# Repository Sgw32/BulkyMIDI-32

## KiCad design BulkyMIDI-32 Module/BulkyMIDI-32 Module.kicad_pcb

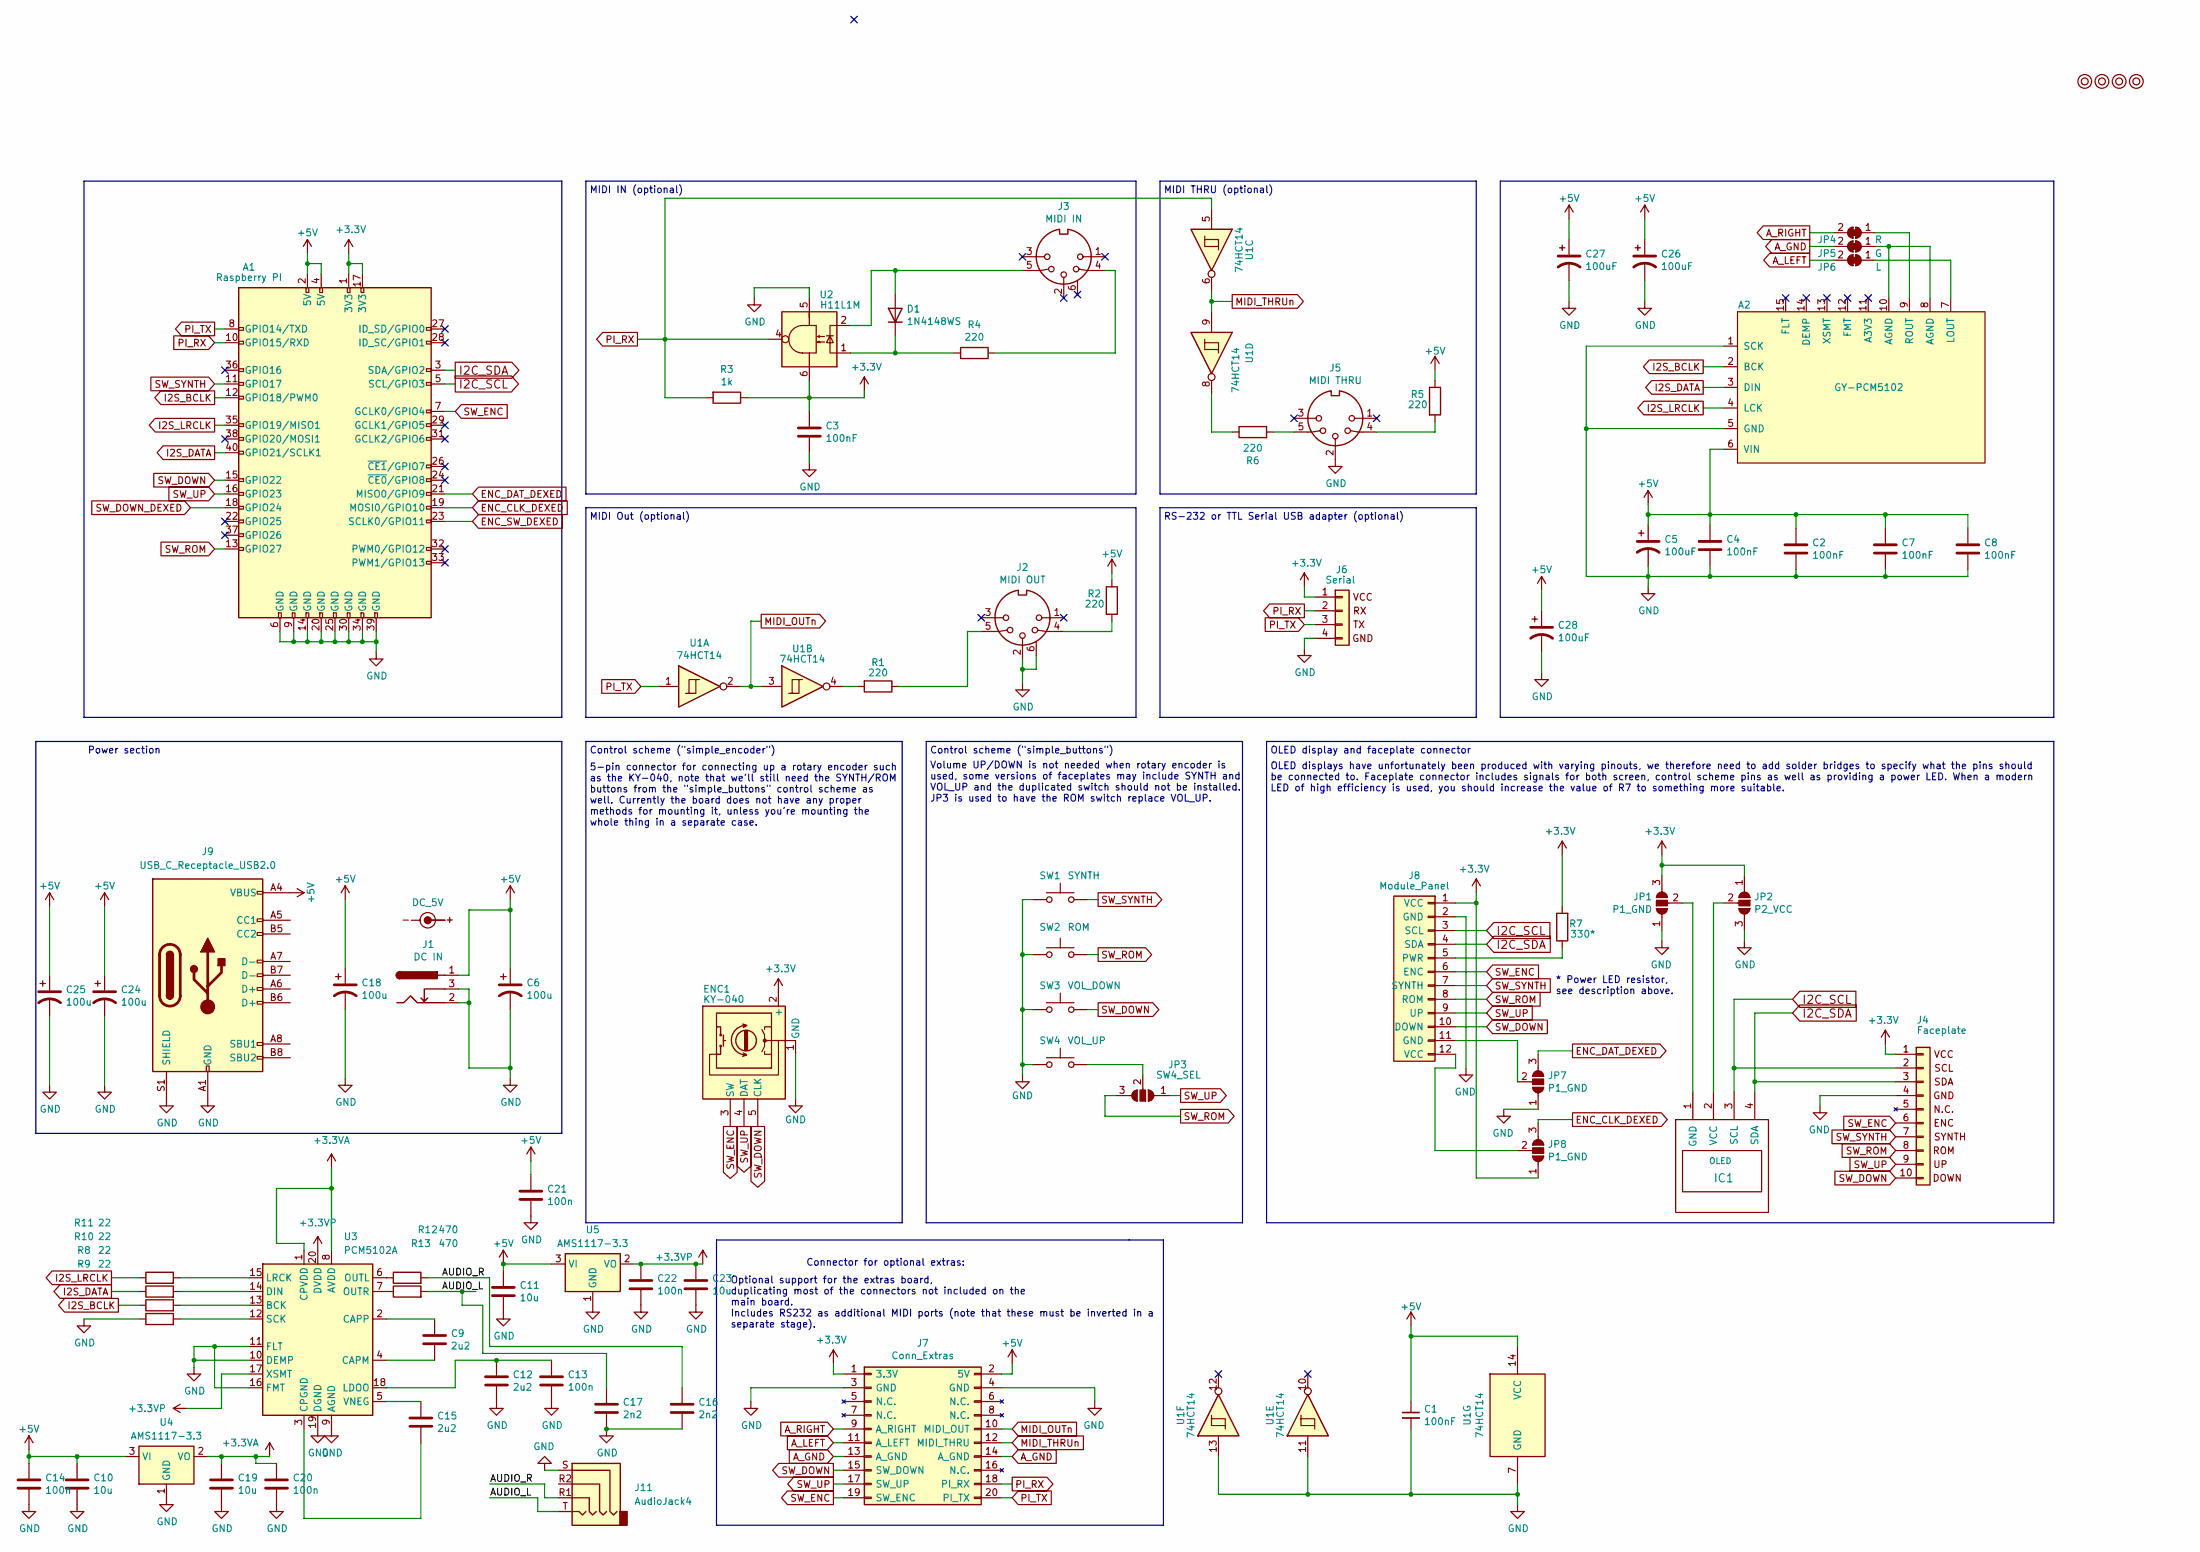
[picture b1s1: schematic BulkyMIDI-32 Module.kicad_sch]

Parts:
A1: Raspberry PI; Raspberry_Pi_3B_Socketed_THT_FaceDown_MountingHoles
A2: GY-PCM5102
C1, C2, C3, C4, C7, C8: 100nF; C_0402_1005Metric
C5, C26, C27, C28: 100uF; CP_EIA-3528-21_Kemet-B
C6, C18, C24, C25: 100u; CP_EIA-3528-21_Kemet-B
C9, C12, C15: 2u2; C_0402_1005Metric
C10, C11, C19, C23: 10u; C_0402_1005Metric
C13, C14, C20, C21, C22: 100n; C_0402_1005Metric
C16, C17: 2n2; C_0402_1005Metric
D1: 1N4148WS; D_SOD-323
ENC1: KY-040; PinHeader_1x05_P2.54mm_Horizontal
IC1: OLED; 1.3_I2C_OLED_No_mounting
J1: DC IN; BarrelJack_CLIFF_FC681465S_SMT_Horizontal
J2: MIDI OUT; DIN5_MIDI_OUT
J3: MIDI IN; DIN5_MIDI_IN
J4: Faceplate; PinSocket_1x10_P2.54mm_Vertical
J5: MIDI THRU; PinHeader_1x05_P2.54mm_Horizontal
J6: Serial; PinHeader_1x04_P2.54mm_Horizontal
J7: Conn_Extras; PinSocket_2x10_P2.54mm_Vertical
J8: Module_Panel
J9: USB_C_Receptacle_USB2.0; USB_C_Receptacle_XKB_U262-16XN-4BVC11
J11: AudioJack4; Jack_3.5mm_PJ320D_Horizontal
JP1, JP7, JP8: P1_GND; SolderJumper-3_P1.3mm_Open_RoundedPad1.0x1.5mm
JP2: P2_VCC; SolderJumper-3_P1.3mm_Open_RoundedPad1.0x1.5mm
JP3: SW4_SEL; SolderJumper-3_P1.3mm_Open_RoundedPad1.0x1.5mm
JP4: R; SolderJumper-2_P1.3mm_Open_TrianglePad1.0x1.5mm
JP5: G; SolderJumper-2_P1.3mm_Open_TrianglePad1.0x1.5mm
JP6: L; SolderJumper-2_P1.3mm_Open_TrianglePad1.0x1.5mm
M1, M2, M3, M4: Mounting; M3
R1, R2, R4, R5, R6: 220; R_0805_2012Metric
R3: 1k; R_0805_2012Metric
R7: 330*; R_0805_2012Metric
R8, R9, R10, R11: 22; R_0402_1005Metric
R12, R13: 470; R_0402_1005Metric
SW1: SYNTH; SW_Tactile_SPST_Angled_PTS645Vx39-2LFS
SW2: ROM; SW_Tactile_SPST_Angled_PTS645Vx39-2LFS
SW3: VOL_DOWN; SW_Tactile_SPST_Angled_PTS645Vx39-2LFS
SW4: VOL_UP; SW_Tactile_SPST_Angled_PTS645Vx39-2LFS
SYM1: DC_5V; PWR_Specification
U1: 74HCT14; SO-14_3.9x8.65mm_P1.27mm
U2: H11L1M; DIP-6_W7.62mm
U3: PCM5102A; TSSOP-20_4.4x6.5mm_P0.65mm
U4, U5: AMS1117-3.3; SOT-223-3_TabPin2

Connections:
+3.3VA: C19.1, C20.1, U3.1 (CPVDD), U3.8 (AVDD), U4.2 (VO)
+3.3VP: C22.1, C23.1, U3.17 (XSMT), U3.20 (DVDD), U5.2 (VO)
+3V3: A1.1 (3V3), A1.17 (3V3), C3.1, ENC1.2 (+), J4.1 (VCC), J6.1, J7.1 (3.3V), J8.1 (VCC), JP1.3 (B), JP2.1 (A), JP8.1 (A), R3.1, R7.2, U2.6
+5V: A1.2 (5V), A1.4 (5V), A2.6 (VIN), C1.1, C2.1, C4.1, C5.1, C6.1, C7.1, C8.1, C10.1, C11.1, C14.1, C18.1, C21.1, C24.1, C25.1, C26.1, C27.1, C28.1, J1.1, J7.2 (5V), J9.A4 (VBUS), J9.A9 (VBUS), J9.B4 (VBUS), J9.B9 (VBUS), R2.1, R5.1, U1.14 (VCC), U4.3 (VI), U5.3 (VI)
/AUDIO_L: C17.1, J11.T, R13.2
/AUDIO_R: C16.1, J11.R1, R12.2
A_GND: J7.13 (A_GND), J7.14 (A_GND), JP5.2 (B)
A_LEFT: J7.11 (A_LEFT), JP6.2 (B)
A_RIGHT: J7.9 (A_RIGHT), JP4.2 (B)
ENC_CLK_DEXED: A1.19 (MOSI0/GPIO10), JP8.3 (B)
ENC_DAT_DEXED: A1.21 (MISO0/GPIO9), JP7.3 (B)
ENC_SW_DEXED: A1.23 (SCLK0/GPIO11)
GND: A1.6 (GND), A1.9 (GND), A1.14 (GND), A1.20 (GND), A1.25 (GND), A1.30 (GND), A1.34 (GND), A1.39 (GND), A2.1 (SCK), A2.5 (GND), C1.2, C2.2, C3.2, C4.2, C5.2, C6.2, C7.2, C8.2, C10.2, C11.2, C12.2, C13.2, C14.2, C16.2, C17.2, C18.2, C19.2, C20.2, C21.2, C22.2, C23.2, C24.2, C25.2, C26.2, C27.2, C28.2, ENC1.1 (GND), J1.2, J1.3, J2.2, J2.6, J4.4, J5.2, J6.4, J7.3 (GND), J7.4 (GND), J8.2 (GND), J9.A1 (GND), J9.A12 (GND), J9.B1 (GND), J9.B12 (GND), J9.S1 (SHIELD), J11.S, JP1.1 (A), JP2.3 (B), JP7.1 (A), R11.1, SW1.1, SW2.1, SW3.1, SW4.1, U1.7 (GND), U1.11, U1.13, U2.5, U3.9 (AGND), U3.10 (DEMP), U3.11 (FLT), U3.16 (FMT), U3.19 (DGND), U4.1 (GND), U5.1 (GND)
I2C_SCL: A1.5 (SCL/GPIO3), IC1.3 (SCL), J4.2, J8.3 (SCL)
I2C_SDA: A1.3 (SDA/GPIO2), IC1.4 (SDA), J4.3, J8.4 (SDA)
I2S_BCLK: A1.12 (GPIO18/PWM0), A2.2 (BCK), R10.1
I2S_DATA: A1.40 (GPIO21/SCLK1), A2.3 (DIN), R9.1
I2S_LRCLK: A1.35 (GPIO19/MISO1), A2.4 (LCK), R8.1
MIDI_OUTn: J7.10 (MIDI_OUT), U1.2, U1.3
MIDI_THRUn: J7.12 (MIDI_THRU), U1.6, U1.9
unnamed: A2.7 (LOUT), JP6.1 (A)
unnamed: A2.9 (ROUT), JP4.1 (A)
unnamed: D1.2 (A), J3.5, U2.2
unnamed: D1.1 (K), R4.2, U2.1
unnamed: IC1.1 (GND), JP1.2 (C)
unnamed: IC1.2 (VCC), JP2.2 (C)
unnamed: J2.4, R2.2
unnamed: J2.5, R1.1
unnamed: J3.4, R4.1
unnamed: J5.4, R5.2
unnamed: J5.5, R6.2
unnamed: J8.5 (PWR), R7.1
unnamed: JP3.2 (C), SW4.2
unnamed: A2.8 (AGND), A2.10 (AGND), JP5.1 (A)
unnamed: J8.11 (GND), JP7.2 (C)
unnamed: J8.12 (VCC), JP8.2 (C)
unnamed: R1.2, U1.4
unnamed: R6.1, U1.8
unnamed: R10.2, U3.13 (BCK)
unnamed: C9.2, U3.4 (CAPM)
unnamed: C9.1, U3.2 (CAPP)
unnamed: C15.2, U3.3 (CPGND)
unnamed: R9.2, U3.14 (DIN)
unnamed: C12.1, C13.1, U3.18 (LDOO)
unnamed: R8.2, U3.15 (LRCK)
unnamed: R12.1, U3.6 (OUTL)
unnamed: R13.1, U3.7 (OUTR)
unnamed: R11.2, U3.12 (SCK)
unnamed: C15.1, U3.5 (VNEG)
PI_RX: A1.10 (GPIO15/RXD), J6.2, J7.18 (PI_RX), R3.2, U1.5, U2.4
PI_TX: A1.8 (GPIO14/TXD), J6.3, J7.20 (PI_TX), U1.1
SW_DOWN: A1.15 (GPIO22), ENC1.5 (CLK), J4.10 (GND), J7.15 (SW_DOWN), J8.10 (DOWN), SW3.2
SW_DOWN_DEXED: A1.18 (GPIO24)
SW_ENC: A1.7 (GCLK0/GPIO4), ENC1.3 (SW), J4.6, J7.19 (SW_ENC), J8.6 (ENC)
SW_ROM: A1.13 (GPIO27), J4.8, J8.8 (ROM), JP3.3 (B), SW2.2
SW_SYNTH: A1.11 (GPIO17), J4.7, J8.7 (SYNTH), SW1.2
SW_UP: A1.16 (GPIO23), ENC1.4 (DAT), J4.9, J7.17 (SW_UP), J8.9 (UP), JP3.1 (A)

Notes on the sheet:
OLED display and faceplate connector
Control scheme ("simple_buttons")
MIDI Out (optional)
Control scheme ("simple_encoder")
MIDI THRU (optional)
Power section
Connector for optional extras:
MIDI IN (optional)
5-pin connector for connecting up a rotary encoder such as the KY-040, note that we'll still need the SYNTH/ROM buttons from the "simple_buttons" control scheme as well. Currently the board does not have any proper methods for mounting it, unless you're mounting the whole thing in a separate case.
Optional support for the extras board, duplicating most of the connectors not included on the main board. Includes RS232 as additional MIDI ports (note that these must be inverted in a separate stage).
Volume UP/DOWN is not needed when rotary encoder is used, some versions of faceplates may include SYNTH and VOL_UP and the duplicated switch should not be installed. JP3 is used to have the ROM switch replace VOL_UP.
RS-232 or TTL Serial USB adapter (optional)
* Power LED resistor, see description above.
OLED displays have unfortunately been produced with varying pinouts, we therefore need to add solder bridges to specify what the pins should be connected to. Faceplate connector includes signals for both screen, control scheme pins as well as providing a power LED. When a modern LED of high efficie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

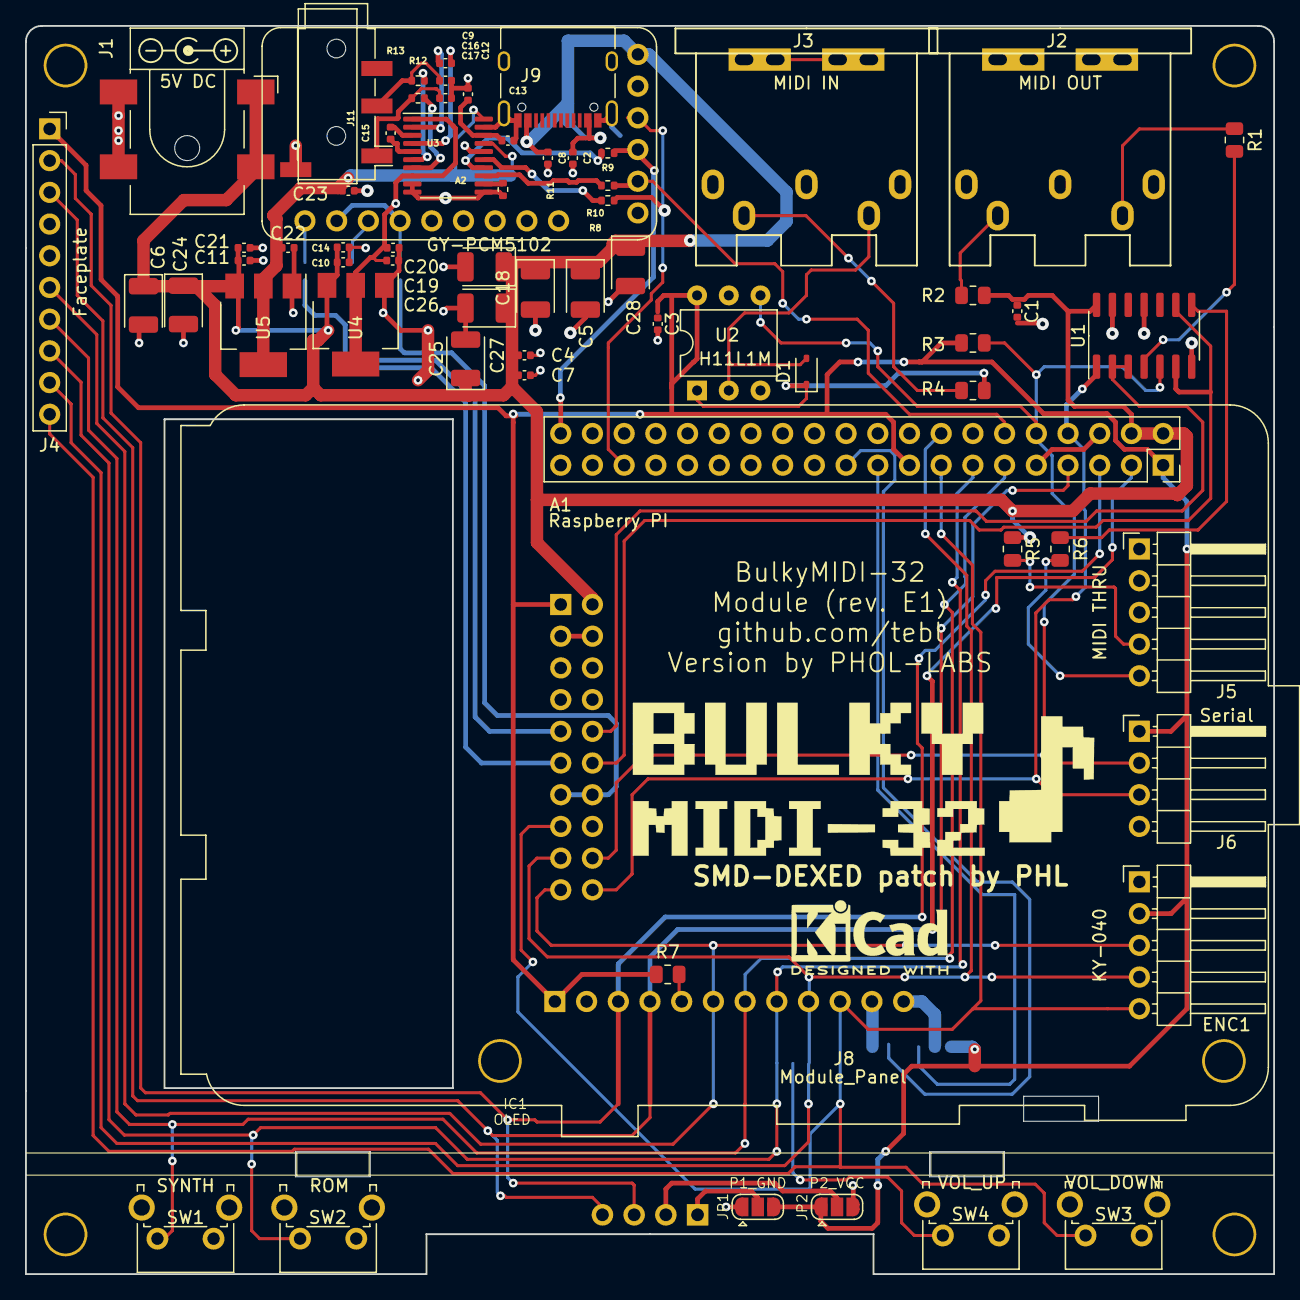
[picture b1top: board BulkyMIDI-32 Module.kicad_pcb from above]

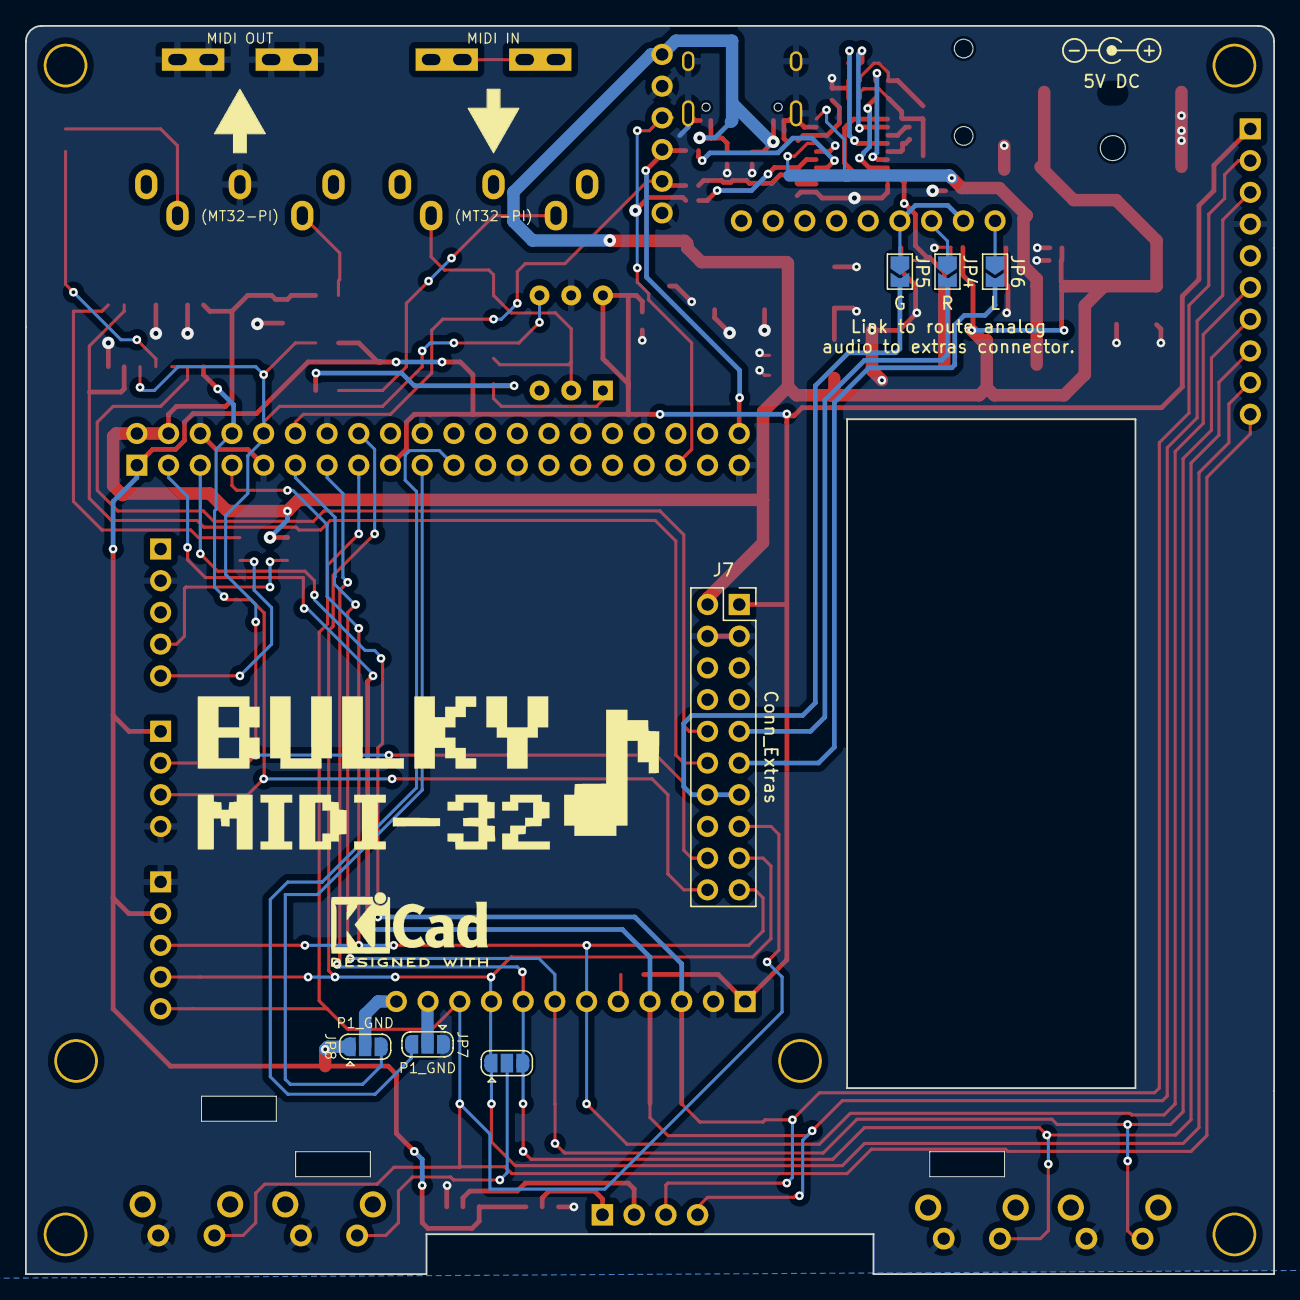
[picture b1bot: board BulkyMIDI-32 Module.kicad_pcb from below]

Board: 2 copper layers, 100.0 x 100.0 mm, 78 parts (7 on the bottom side), 55 nets.

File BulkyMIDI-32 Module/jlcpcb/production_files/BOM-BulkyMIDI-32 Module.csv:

Comment,Designator,Footprint,LCSC
PCM5102A,U3,TSSOP-20_4.4x6.5mm_P0.65mm,C107671
DC IN,J1,BarrelJack_CLIFF_FC681465S_SMT_Horizontal,C114916
2u2,"C12,C15,C9",C_0402_1005Metric,C12530
Raspberry PI,A1,Raspberry_Pi_3B_Socketed_THT_FaceDown_MountingHoles,C132132
100nF,"C1,C13,C14,C2,C20,C21,C22,C3,C4,C7,C8",C_0402_1005Metric,C1525
2n2,"C16,C17",C_0402_1005Metric,C1531
10u,"C10,C11,C19,C23",C_0402_1005Metric,C15525
100u,"C18,C24,C25,C26,C27,C28,C5,C6",CP_EIA-3528-21_Kemet-B,C16133
H11L1M,U2,DIP-6_W7.62mm,C16587
USB_C_Receptacle_USB2.0,J9,USB_C_Receptacle_XKB_U262-16XN-4BVC11,C165948
1k,R3,R_0805_2012Metric,C17513
220,"R1,R2,R4,R5,R6",R_0805_2012Metric,C17557
330*,R7,R_0805_2012Metric,C17630
1N4148WS,D1,D_SOD-323,C2128
Module_Panel,J8,Module_Panel,C247920
22,"R10,R11,R8,R9",R_0402_1005Metric,C25092
470,"R12,R13",R_0402_1005Metric,C25117
MIDI OUT,"J2,J3",DIN5_MIDI_OUT,C2939344
74HCT14,U1,SO-14_3.9x8.65mm_P1.27mm,C5967
AMS1117-3.3,"U4,U5",SOT-223-3_TabPin2,C6186
AudioJack4,J11,Jack_3.5mm_PJ320D_Horizontal,C95562
Mounting,M1,M3,
Mounting,M2,M3,
Mounting,M3,M3,
Mounting,M4,M3,
Faceplate,J4,PinSocket_1x10_P2.54mm_Vertical,
P1_GND,JP1,SolderJumper-3_P1.3mm_Open_RoundedPad1.0x1.5mm,
P2_VCC,JP2,SolderJumper-3_P1.3mm_Open_RoundedPad1.0x1.5mm,
VOL_UP,SW4,SW_Tactile_SPST_Angled_PTS645Vx39-2LFS,
DC_5V,SYM1,PWR_Specification,
KY-040,ENC1,PinHeader_1x05_P2.54mm_Horizontal,
MIDI THRU,J5,PinHeader_1x05_P2.54mm_Horizontal,
Serial,J6,PinHeader_1x04_P2.54mm_Horizontal,
GY-PCM5102,A2,GY-PCM5102,
ROM,SW2,SW_Tactile_SPST_Angled_PTS645Vx39-2LFS,
OLED,IC1,1.3_I2C_OLED_No_mounting,
SYNTH,SW1,SW_Tactile_SPST_Angled_PTS645Vx39-2LFS,
VOL_DOWN,SW3,SW_Tactile_SPST_Angled_PTS645Vx39-2LFS,
SW4_SEL,JP3,SolderJumper-3_P1.3mm_Open_RoundedPad1.0x1.5mm,
Conn_Extras,J7,PinSocket_2x10_P2.54mm_Vertical,
R,JP4,SolderJumper-2_P1.3mm_Open_TrianglePad1.0x1.5mm,
G,JP5,SolderJumper-2_P1.3mm_Open_TrianglePad1.0x1.5mm,
L,JP6,SolderJumper-2_P1.3mm_Open_TrianglePad1.0x1.5mm,
P1_GND,JP7,SolderJumper-3_P1.3mm_Open_RoundedPad1.0x1.5mm,
P1_GND,JP8,SolderJumper-3_P1.3mm_Open_RoundedPad1.0x1.5mm,

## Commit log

2025-11-13 Type C patched
2026-03-25 Add jlc files + SH1106 Dexed
2026-03-25 Compact and integrated DAC with both MT32Pi and Dexed support
